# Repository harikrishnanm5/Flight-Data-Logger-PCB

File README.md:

# Crash-Safe UAV Flight Data Logger PCB

-0277BD?style=flat-square)

A compact **50.0 × 50.0 mm, 4-layer** crash-safe UAV flight data logger ("black box") hardware design built on the standard **30.5 × 30.5 mm M3 flight-controller stack** footprint.

Designed around an **STM32F446RET6** Cortex-M4F MCU, **ESP32-WROOM-32E** Wi-Fi/BLE telemetry module, **6-axis IMU + barometer**, dual **SPI FRAM + MicroSD** storage, an **ideal-diode PowerPath + 1.0 F supercapacitor** backup stage, hardware **3.00 V power-fail detection**, and a high-intensity optical recovery beacon.

---

## Key Features

- **Crash-Safe Power Holdup & Brownout Trigger**:
  - 3.7 V Li-ion input (`J1`) protected by a reverse-polarity P-MOSFET (`Q1`, `AO3401A`).
  - Dual `LTC4412ES6` ideal-diode PowerPath controllers (`U7`/`Q2` and `U8`/`Q3`) seamlessly OR-ing the main battery (`V_BAT_PROT`) and a **5.5 V / 1.0 F backup supercapacitor** (`C_SC1`) onto `V_SYS`.
  - Slew-limited supercapacitor charger (`U11`, `AP22814AW5`) with current-limiting resistor (`R24`, 15 Ω) and Schottky blocking diode (`D4`, `B5819W`).
  - High-efficiency 3.3 V / 2 A synchronous buck regulator (`U6`, `TPS62822DLC`) with shielded `1.0 µH` inductor (`L1`) and filtered `+3.3VA` analog rail (`FB1`).
  - Precision **3.00 V Power-Fail Detect (PFD)** comparator (`U9`, `TLV7031DBV`) referenced against a 2.500 V shunt reference (`U10`, `LM4040DBZ-2.5`) asserting `PFD_INT` on MCU `EXTI1` to flush telemetry before holdup collapse.
  - 0.1%-tolerance battery voltage sensing divider (`R1`/`R2` -> `V_BAT_ADC`).
- **Dual-Tier Flight Recording**:
  - **2 Mbit SPI FRAM** (`U5`, `CY15B102QN-50SXIT`) for deterministic, zero-wear, instant-write black-box buffering during power loss.
  - **Push-Pull MicroSD Socket** (`J3`, Hirose `DM3D-SF`) on `SPI1` with card-detect (`SD_CD`) and pull-ups.
- **Flight Sensors**:
  - **6-Axis IMU** (`U3`, `MPU-6050`, I2C `0x68`) with dedicated `MPU_INT` line.
  - **Barometric Pressure Sensor** (`U4`, `BMP280`, I2C `0x76`).
- **Telemetry & Recovery Beacon**:
  - **ESP32-WROOM-32E-N4** (`U2`) wired to `USART1` (`R16`/`R17` series resistors) with dedicated PCB top-edge antenna keepout zone (`y < 6.25 mm`).
  - **High-intensity red optical beacon LED** (`D1`, `SM2835-RED-HI`) switched via N-MOSFET (`Q4`, `2N7002`).

---

## System Architecture

```mermaid
flowchart LR
    BATT["3.7V Li-ion Input (J1)"] --> RVP["Reverse-Polarity PFET (Q1)"]
    RVP --> CHG["Supercap Charger (U11 + R24 + D4)"]
    CHG --> SCAP["1.0F 5.5V Supercap (C_SC1)"]

    RVP --> OR1["Ideal Diode Ctrl (U7 + Q2)"]
    SCAP --> OR2["Ideal Diode Ctrl (U8 + Q3)"]
    OR1 --> VSYS["V_SYS"]
    OR2 --> VSYS

    VSYS --> BUCK["3.3V 2A Buck (U6 TPS62822 + L1)"]
    BUCK --> V33["+3V3 Plane (In2.Cu)"]
    V33 --> FB["Ferrite Bead (FB1)"] --> V33A["+3.3VA Analog"]

    RVP --> PFD["3.00V PFD (U9 TLV7031 + U10 LM4040)"]
    RVP --> ADC["0.1% Divider (R1/R2)"]
    PFD -->|PFD_INT| MCU["STM32F446RET6 (U1)"]
    ADC -->|V_BAT_ADC| MCU

    MCU <-->|I2C1| IMU["MPU-6050 (U3)"]
    MCU <-->|I2C1| BARO["BMP280 (U4)"]
    MCU <-->|SPI1| FRAM["2Mbit FRAM (U5)"]
    MCU <-->|SPI1| SD["MicroSD (J3)"]
    MCU <-->|USART1| ESP["ESP32-WROOM-32E (U2)"]
    MCU -->|BEACON_CTRL| BEACON["Q4 + D1 Beacon LED"]
```

---

## PCB & Stackup Specifications

| Parameter | Specification |
| :--- | :--- |
| **Board Outline** | 50.0 × 50.0 mm, 2.5 mm corner radius |
| **Thickness** | 1.6 mm |
| **Mounting Pattern** | 30.5 × 30.5 mm M3 (`H1`–`H4`, 3.2 mm drill, 6.4 mm grounded pad) |
| **Copper Layers** | **4 Layers** (`F.Cu`, `In1.Cu`, `In2.Cu`, `B.Cu`) |
| **Layer 1 (`F.Cu`)** | Top components (42 footprints), signals, `GND` copper pour |
| **Layer 2 (`In1.Cu`)** | Solid `GND` reference plane |
| **Layer 3 (`In2.Cu`)** | `+3V3` power plane |
| **Layer 4 (`B.Cu`)** | Bottom components (59 footprints), signals, `GND` copper pour |
| **PCB Geometry Counts** | 101 footprints, 848 track segments, 272 vias, 4 copper zones, 57 nets |
| **Min Clearance / Edge** | 0.20 mm clearance / 0.30 mm copper-to-edge clearance |
| **Min Track / Via** | 0.15 mm track / 0.45 mm via dia (0.20 mm drill, 0.125 mm annular ring) |
| **Hole-to-Hole Clearance** | 0.50 mm minimum |

---

## Key Components

> Full 51-line / 101-footprint bill of materials is available in [`BOM.csv`](BOM.csv) (97 electrical components + 4 grounded M3 mounting holes).

| Ref | Part / Value | MPN | Side | Function |
| :--- | :--- | :--- | :--- | :--- |
| `U1` | `STM32F446RET6` | `STM32F446RET6` | Top | ARM Cortex-M4F MCU (180 MHz, 512 KB Flash, LQFP-64) |
| `U2` | `ESP32-WROOM-32` | `ESP32-WROOM-32E-N4` | Top | Wi-Fi / BLE Telemetry Module |
| `U3` | `MPU-6050` | `MPU-6050` | Top | 6-Axis IMU (`I2C1` `0x68`) |
| `U4` | `BMP280` | `BMP280` | Top | Barometric Pressure Sensor (`I2C1` `0x76`) |
| `U5` | `CY15B102QN-50SXIT` | `CY15B102QN-50SXIT` | Bottom | 2 Mbit SPI FRAM Non-Volatile Buffer |
| `U6` | `TPS62822DLC` | `TPS62822DLCR` | Bottom | 3.3 V 2 A Synchronous Buck Regulator |
| `U7`, `U8` | `LTC4412ES6` | `LTC4412ES6#TRPBF` | Bottom | Battery & Supercap Ideal Diode OR-ing Controllers |
| `U9` | `TLV7031DBV` | `TLV7031DBVR` | Bottom | Power-Fail Detect Comparator (3.00 V Trip) |
| `U10` | `LM4040DBZ-2.5` | `LM4040AIM3-2.5` | Bottom | 2.500 V Precision Shunt Reference |
| `U11` | `AP22814AW5` | `AP22814AW5-7` | Bottom | Slew-Limited Supercapacitor Charge Switch |
| `C_SC1` | `1.0F 5.5V` | `DX-5R5V105U` | Top (THT) | 5.5 V 1.0 F Backup Supercapacitor |
| `J3` | `MicroSD_SPI` | `DM3D-SF` | Top | Push-Pull MicroSD Card Socket (`SPI1`) |
| `J1` | `JST_PH_BATT` | `B2B-PH-K-S` | Top (THT) | 3.7 V Li-ion Input Header |
| `J2` | `SWD_5P` | `HDR-1x5-2.54` | Top (THT) | SWD Debug Header (`3V3`, `SWCLK`, `GND`, `SWDIO`, `NRST`) |
| `J4` | `ESP_UART_6P` | `HDR-1x6-1.27` | Top (THT) | ESP32 UART/Flash Header |
| `D1` | `BEACON_LED_HI` | `SM2835-RED-HI` | Top | High-Intensity Optical Emergency Beacon LED |

---

## Repository Structure

```text
.
├── FlightDataLogger.kicad_pro          # KiCad project & DRC/netclass settings
├── FlightDataLogger.kicad_sch          # KiCad schematic (A2 sheet)
├── FlightDataLogger.kicad_pcb          # KiCad 4-layer PCB layout
├── BOM.csv                             # Complete BOM generated from design_spec.py
├── layers/                             # Exported copper & outline plots (PDF / SVG)
│   ├── FlightDataLogger-F_Cu.pdf
│   ├── FlightDataLogger-F_Cu.svg
│   ├── FlightDataLogger-In1_Cu.pdf
│   ├── FlightDataLogger-In2_Cu.pdf
│   ├── FlightDataLogger-B_Cu.pdf
│   ├── FlightDataLogger-Edge_Cuts.pdf
│   └── FlightDataLogger-Edge_Cuts.svg
└── scripts/                            # Programmatic KiCad generation & verification
    ├── design_spec.py                  # Single source of truth (board, components, nets)
    ├── generate_project_and_schematic.py
    ├── generate_pcb.py                 # KiCad pcbnew API generator + Pathfinder A* router
    └── verify_placement.py             # Footprint, bounds, keepout & courtyard checker
```

---

## Layer Plots

Exported fabrication layer plots are available in [`layers/`](layers/):

- Top Copper (`F.Cu`): [`FlightDataLogger-F_Cu.pdf`](layers/FlightDataLogger-F_Cu.pdf) | [`FlightDataLogger-F_Cu.svg`](layers/FlightDataLogger-F_Cu.svg)
- Inner 1 (`In1.Cu` — Solid GND): [`FlightDataLogger-In1_Cu.pdf`](layers/FlightDataLogger-In1_Cu.pdf)
- Inner 2 (`In2.Cu` — +3V3 Plane): [`FlightDataLogger-In2_Cu.pdf`](layers/FlightDataLogger-In2_Cu.pdf)
- Bottom Copper (`B.Cu`): [`FlightDataLogger-B_Cu.pdf`](layers/FlightDataLogger-B_Cu.pdf)
- Board Outline (`Edge.Cuts`): [`FlightDataLogger-Edge_Cuts.pdf`](layers/FlightDataLogger-Edge_Cuts.pdf) | [`FlightDataLogger-Edge_Cuts.svg`](layers/FlightDataLogger-Edge_Cuts.svg)

---

## Programmatic Generation & Verification

The hardware files can also be inspected or regenerated programmatically from [`scripts/design_spec.py`](scripts/design_spec.py):

```bash
# 1. Verify footprint loading, bounds, antenna keepout, and courtyard collisions
python scripts/verify_placement.py

# 2. Generate .kicad_pro and .kicad_sch
python scripts/generate_project_and_schematic.py

# 3. Generate .kicad_pcb (run using KiCad's Python environment with pcbnew)
python scripts/generate_pcb.py
```

> **Note:** The generator and verification scripts currently reference local KiCad library directories (`SYM_DIR` / `FP_ROOT` / `FP_DIR` set to `D:\FOSSEE\KiCad\share\kicad\...`) and write KiCad 6.0 `pcbnew` output (while [`FlightDataLogger.kicad_pcb`](FlightDataLogger.kicad_pcb) in this repo has subsequently been updated and saved in KiCad 10.0). Adjust those library paths to match your KiCad installation before re-running the scripts.

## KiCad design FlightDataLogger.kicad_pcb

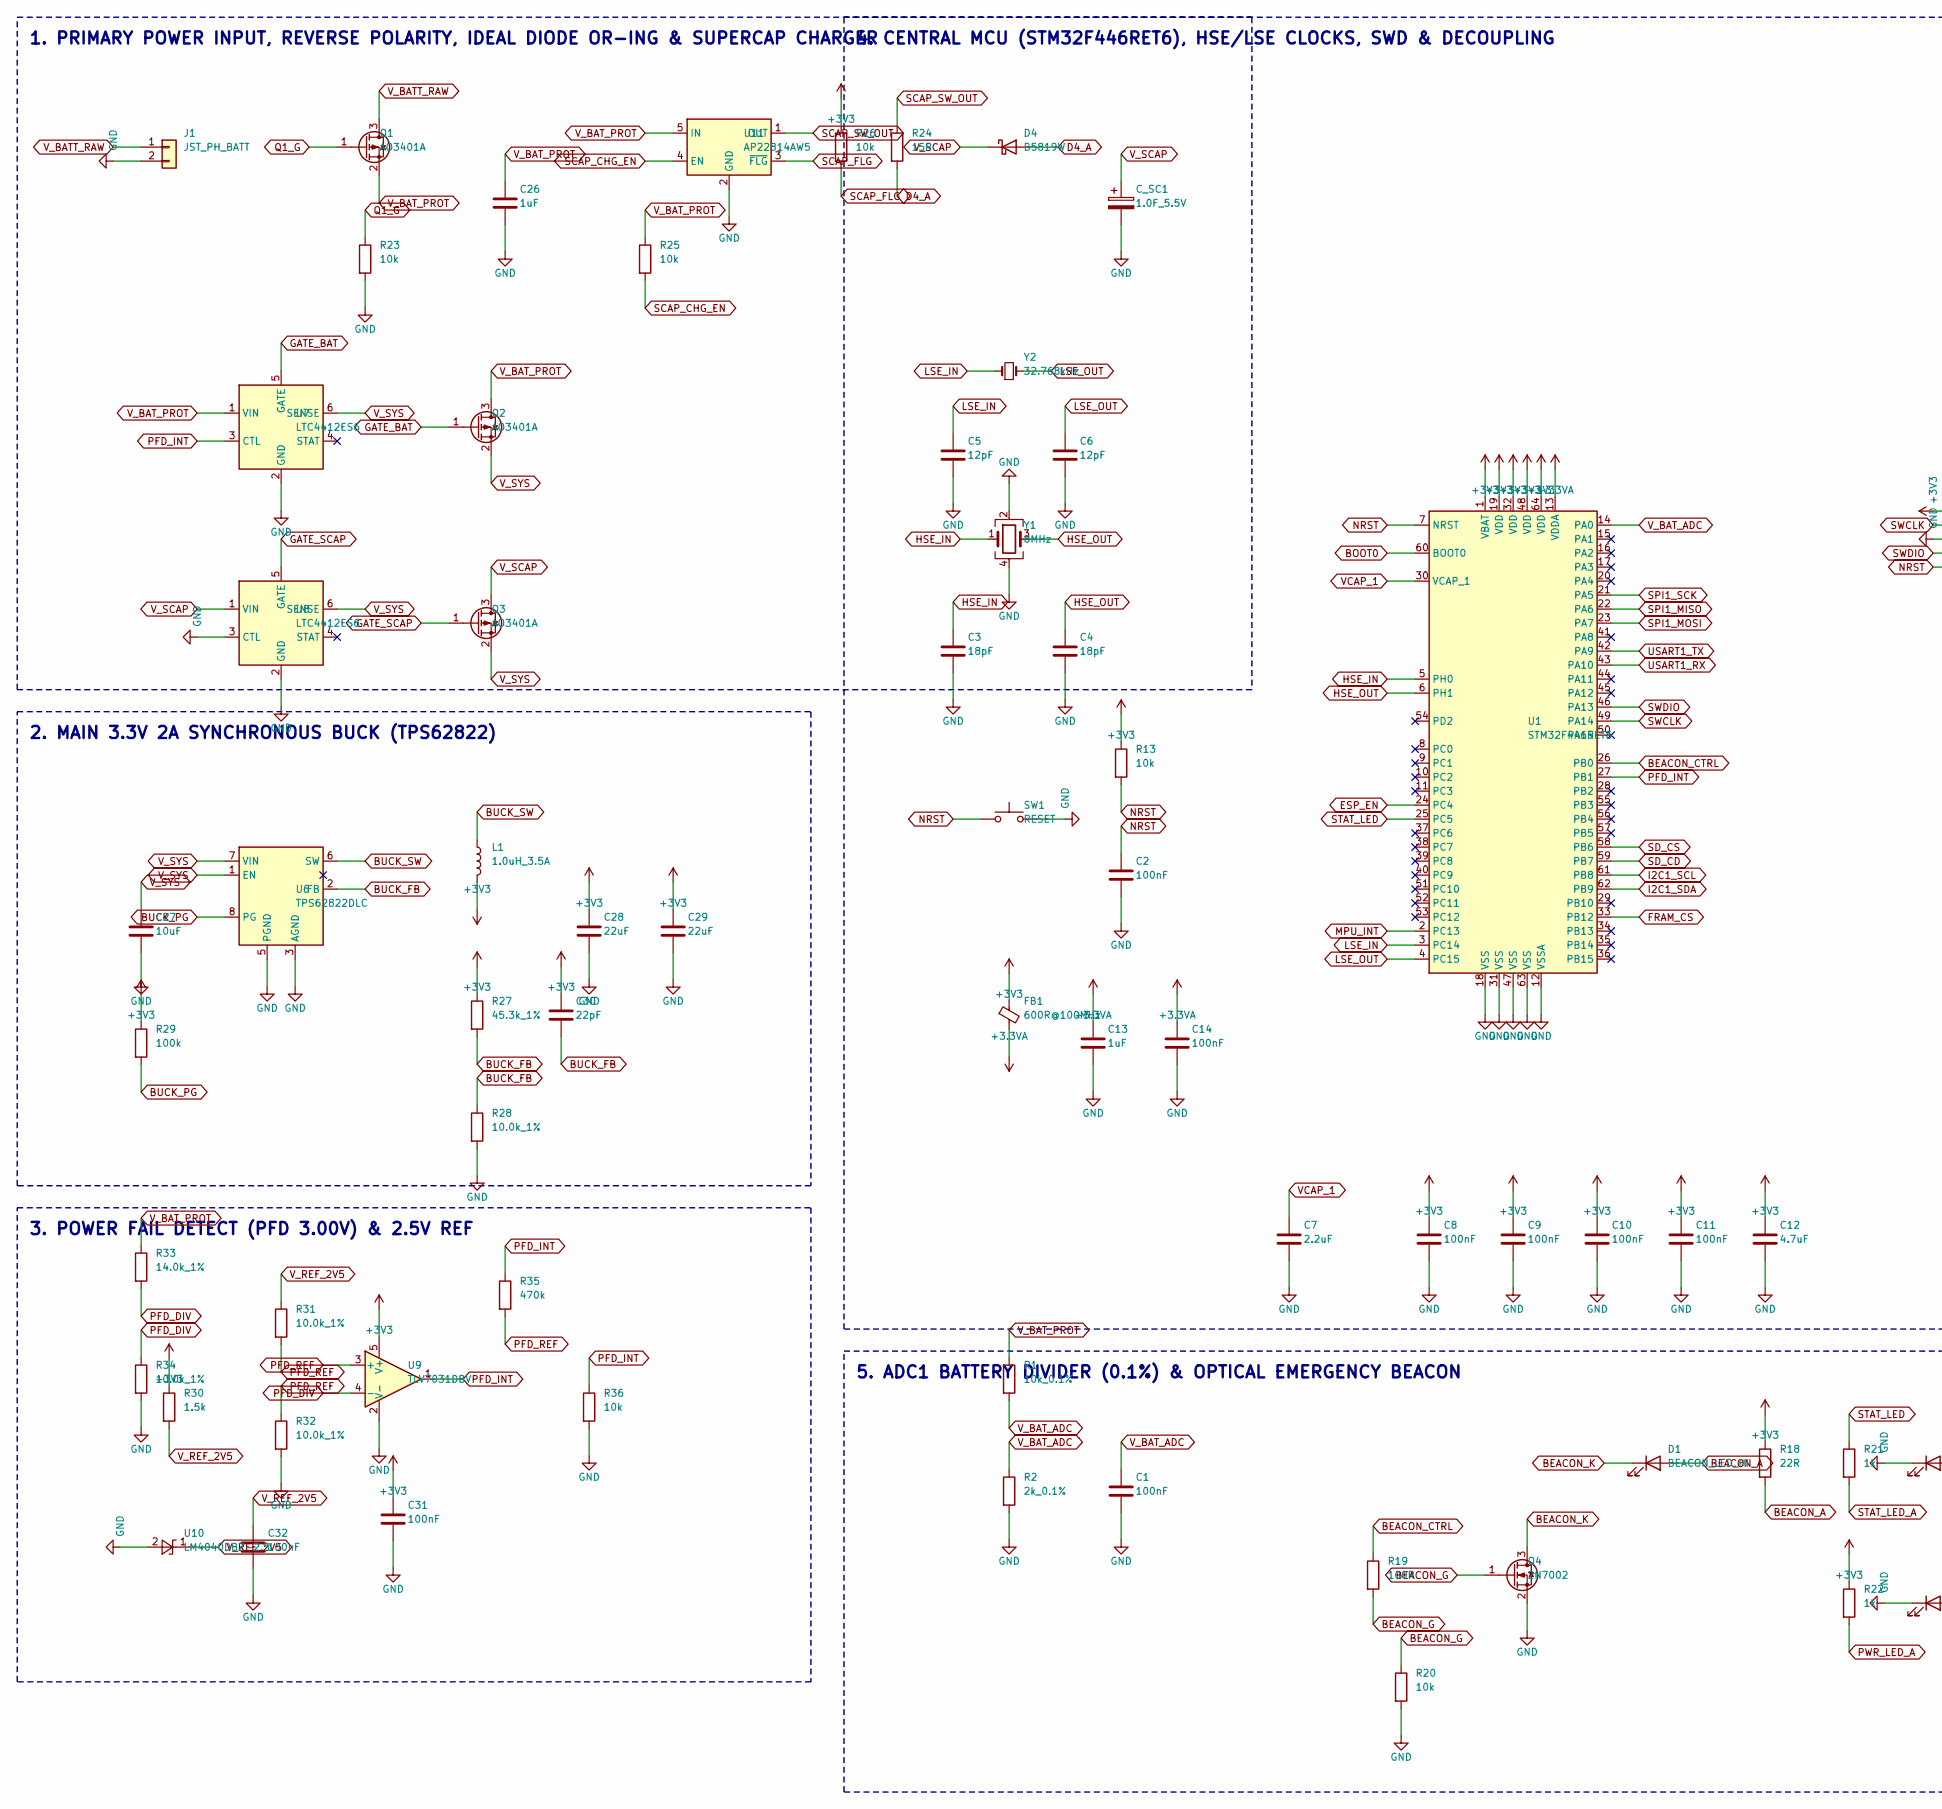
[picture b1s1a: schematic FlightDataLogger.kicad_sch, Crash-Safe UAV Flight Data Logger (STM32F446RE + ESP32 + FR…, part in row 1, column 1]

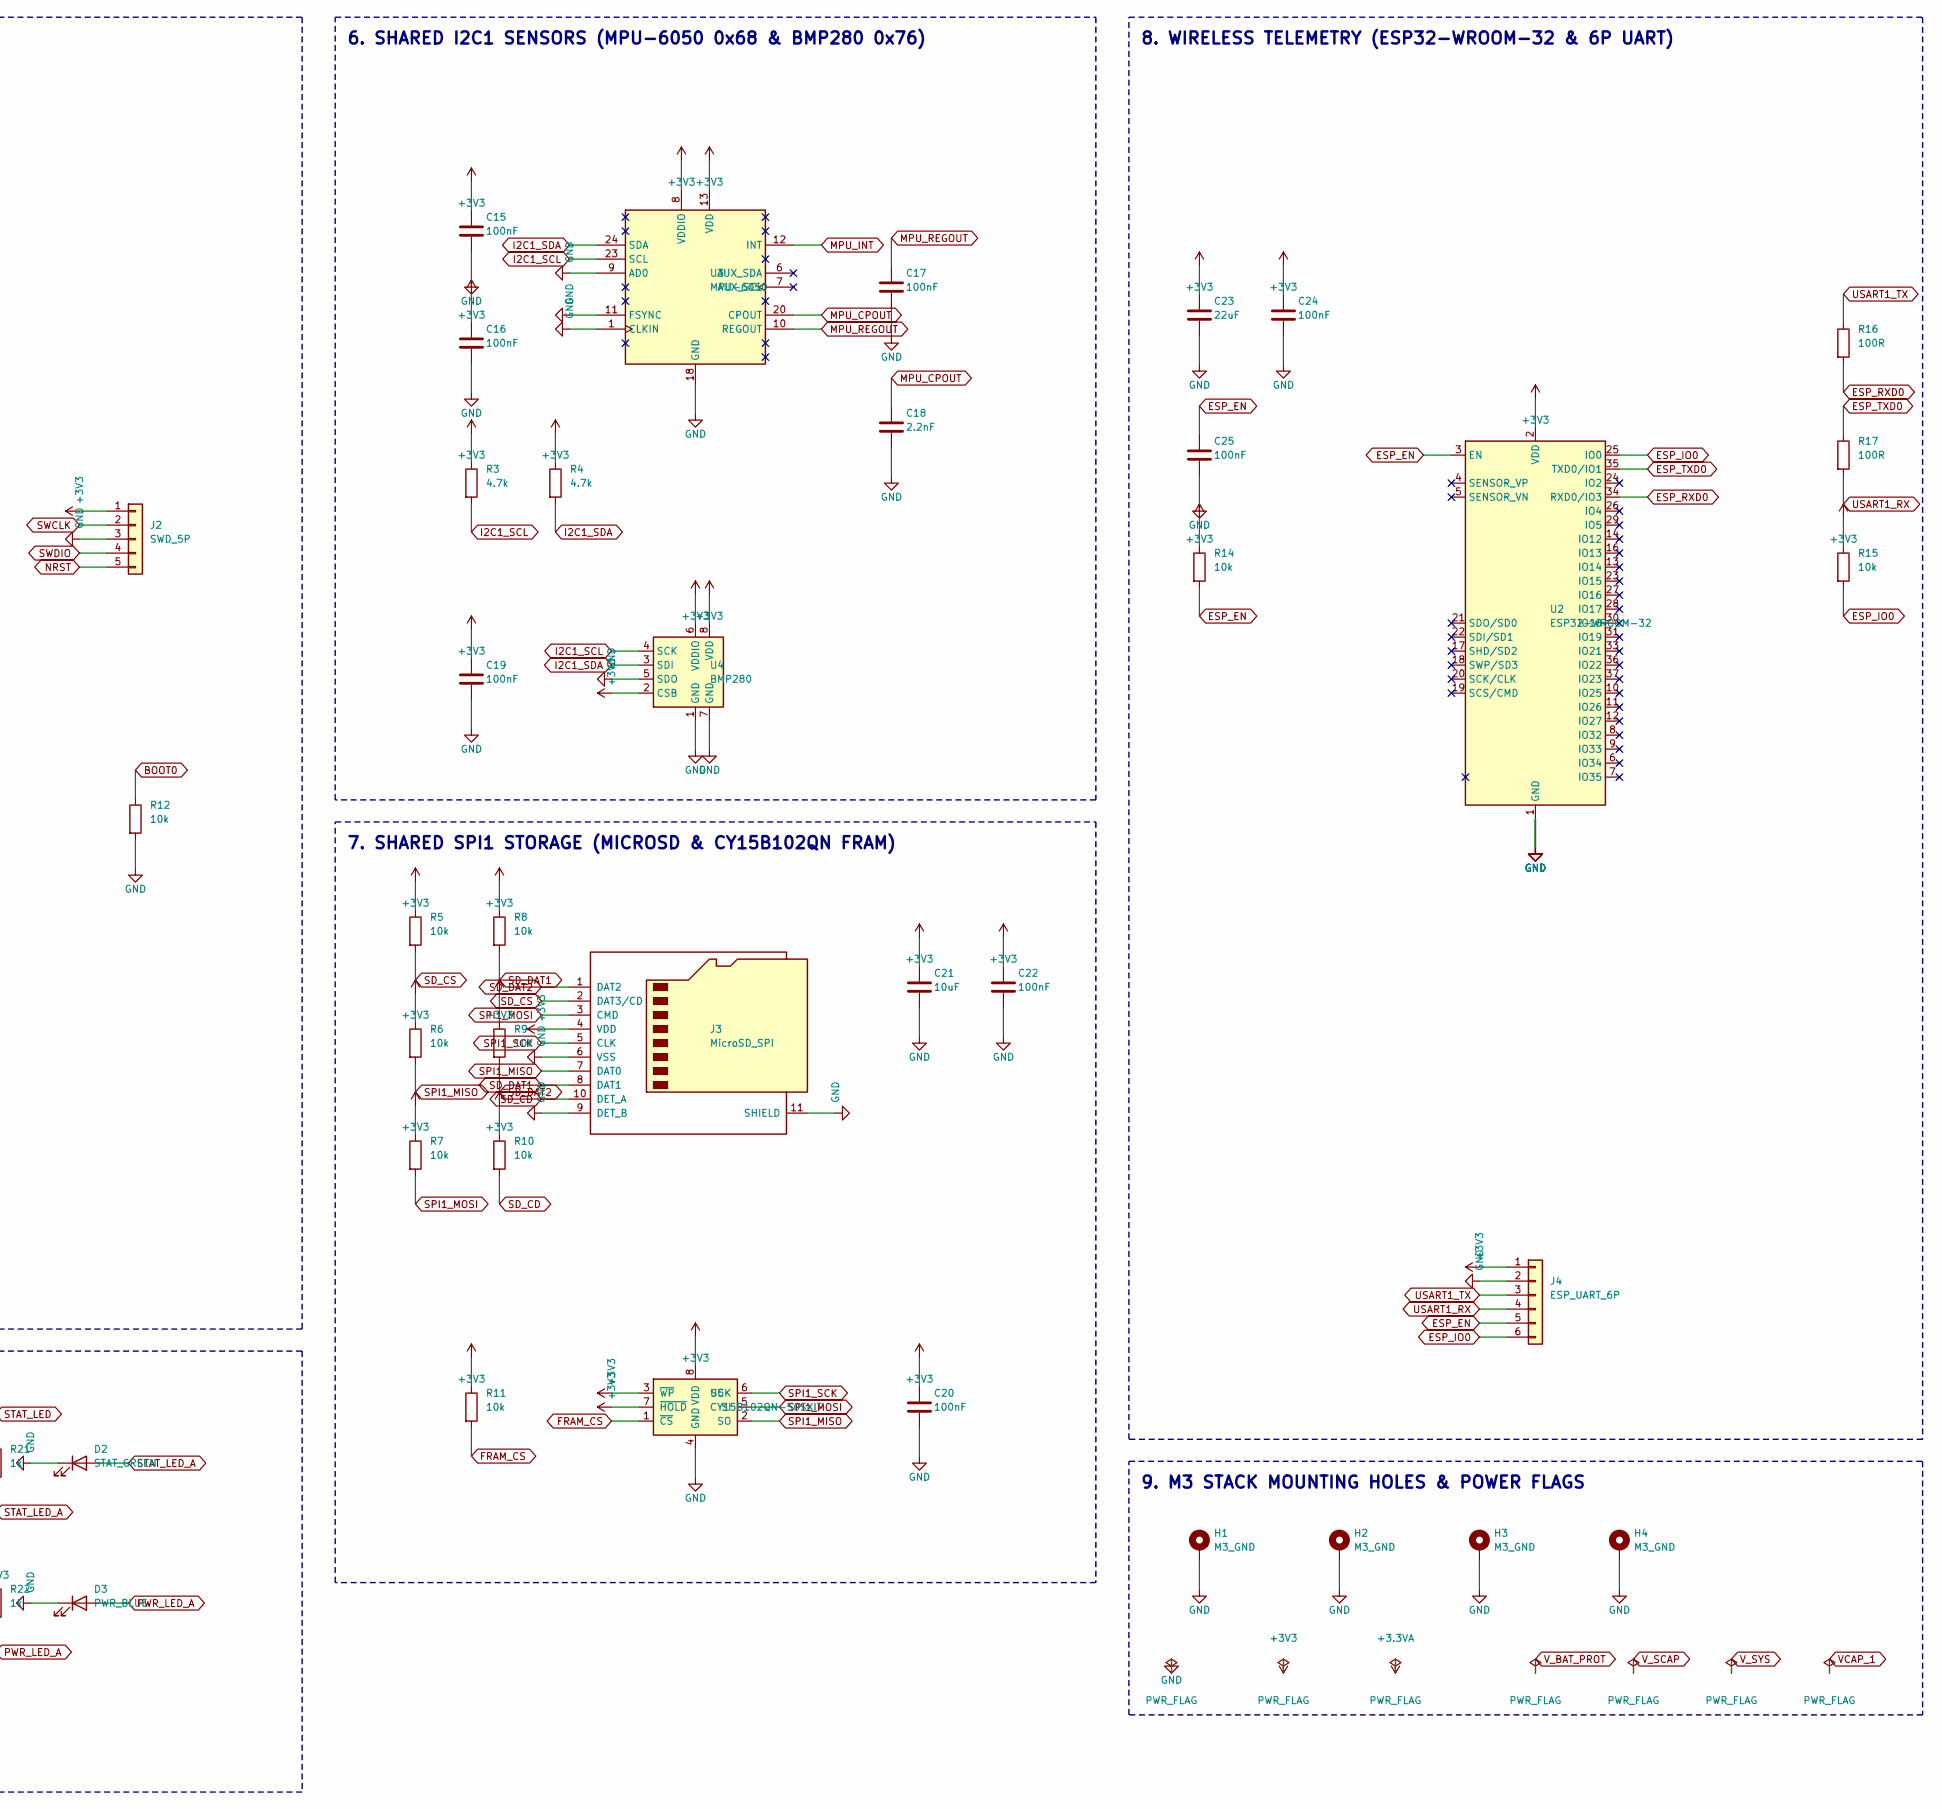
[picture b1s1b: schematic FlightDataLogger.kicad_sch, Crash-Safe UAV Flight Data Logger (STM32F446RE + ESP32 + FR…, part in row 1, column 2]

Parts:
C1, C2, C8, C9, C10, C11, C14, C15, C16, C17, C19, C20, C22, C24, C25, C31, C32: 100nF; C_0603_1608Metric; MPN CC0603KRX7R7BB104
C3, C4: 18pF; C_0603_1608Metric; MPN CC0603JRNPO9BN180
C5, C6: 12pF; C_0603_1608Metric; MPN CC0603JRNPO9BN120
C7: 2.2uF; C_0603_1608Metric; MPN CL10A225KQ8NNNC
C12: 4.7uF; C_0603_1608Metric; MPN CL10A475KQ8NNNC
C13, C26: 1uF; C_0603_1608Metric; MPN CL10A105KB8NNNC
C18: 2.2nF; C_0603_1608Metric; MPN CC0603KRX7R9BB222
C21, C27: 10uF; C_0805_2012Metric; MPN CL21A106KAYNNNE
C23, C28, C29: 22uF; C_0805_2012Metric; MPN CL21A226MAYNNNE
C30: 22pF; C_0603_1608Metric; MPN CC0603JRNPO9BN220
C_SC1: 1.0F_5.5V; DX_5R5VxxxxU_D11.5mm_P5.00mm; MPN DX-5R5V105U
D1: BEACON_LED_HI; LED_PLCC_2835; MPN SM2835-RED-HI
D2: STAT_GREEN; LED_0603_1608Metric; MPN LTST-C190KGKT
D3: PWR_BLUE; LED_0603_1608Metric; MPN LTST-C190TBKT
D4: B5819W; D_SOD-123; MPN B5819W-7-F
FB1: 600R@100MHz; L_0603_1608Metric; MPN BLM18AG601SN1D
H1, H2, H3, H4: M3_GND; MountingHole_3.2mm_M3_Pad_TopBottom; MPN M3_HOLE
J1: JST_PH_BATT; JST_PH_B2B-PH-K_1x02_P2.00mm_Vertical; MPN B2B-PH-K-S
J2: SWD_5P; PinHeader_1x05_P2.54mm_Vertical; MPN HDR-1x5-2.54
J3: MicroSD_SPI; microSD_HC_Hirose_DM3D-SF; MPN DM3D-SF
J4: ESP_UART_6P; PinHeader_1x06_P1.27mm_Vertical; MPN HDR-1x6-1.27
L1: 1.0uH_3.5A; L_Wuerth_MAPI-3015; MPN 74438334010
Q1, Q2, Q3: AO3401A; SOT-23; MPN AO3401A
Q4: 2N7002; SOT-23; MPN 2N7002LT1G
R1: 10k_0.1%; R_0603_1608Metric; MPN ERA-3AEB103V
R2: 2k_0.1%; R_0603_1608Metric; MPN ERA-3AEB202V
R3, R4: 4.7k; R_0603_1608Metric; MPN RC0603FR-074K7L
R5, R6, R7, R8, R9, R10, R11, R12, R13, R14, R15, R20, R23, R25, R26, R36: 10k; R_0603_1608Metric; MPN RC0603FR-0710KL
R16, R17, R19: 100R; R_0603_1608Metric; MPN RC0603FR-07100RL
R18: 22R; R_0805_2012Metric; MPN ERJ-6GEYJ220V
R21, R22: 1k; R_0603_1608Metric; MPN RC0603FR-071KL
R24: 15R; R_0805_2012Metric; MPN ERJ-6GEYJ150V
R27: 45.3k_1%; R_0603_1608Metric; MPN RC0603FR-0745K3L
R28, R31, R32, R34: 10.0k_1%; R_0603_1608Metric; MPN RC0603FR-0710KL
R29: 100k; R_0603_1608Metric; MPN RC0603FR-07100KL
R30: 1.5k; R_0603_1608Metric; MPN RC0603FR-071K5L
R33: 14.0k_1%; R_0603_1608Metric; MPN RC0603FR-0714KL
R35: 470k; R_0603_1608Metric; MPN RC0603FR-07470KL
SW1: RESET; SW_SPST_CK_KXT3; MPN KXT311LHS
U1: STM32F446RET6; LQFP-64_10x10mm_P0.5mm; MPN STM32F446RET6
U2: ESP32-WROOM-32; MPN ESP32-WROOM-32E-N4
U3: MPU-6050; InvenSense_QFN-24_4x4mm_P0.5mm; MPN MPU-6050
U4: BMP280; Bosch_LGA-8_2x2.5mm_P0.65mm_ClockwisePinNumbering; MPN BMP280
U5: CY15B102QN-50SXIT; SOIC-8_3.9x4.9mm_P1.27mm; MPN CY15B102QN-50SXIT
U6: TPS62822DLC; Texas_VSON-HR-8_1.5x2mm_P0.5mm; MPN TPS62822DLCR
U7, U8: LTC4412ES6; TSOT-23-6; MPN LTC4412ES6#TRPBF
U9: TLV7031DBV; SOT-23-5; MPN TLV7031DBVR
U10: LM4040DBZ-2.5; SOT-23; MPN LM4040AIM3-2.5
U11: AP22814AW5; SOT-23-5; MPN AP22814AW5-7
Y1: 8MHz; Crystal_SMD_3225-4Pin_3.2x2.5mm; MPN ABM8-8.000MHZ-B2-T
Y2: 32.768kHz; Crystal_SMD_3215-2Pin_3.2x1.5mm; MPN ABS07-32.768KHZ-T

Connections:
+3.3VA: C13.1, C14.1, FB1.2, U1.13 (VDDA)
+3V3: C8.1, C9.1, C10.1, C11.1, C12.1, C15.1, C16.1, C19.1, C20.1, C21.1, C22.1, C23.1, C24.1, C28.1, C29.1, C30.1, C31.1, FB1.1, J2.1, J3.4 (VDD), J4.1, L1.2, R3.1, R4.1, R5.1, R6.1, R7.1, R8.1, R9.1, R10.1, R11.1, R13.1, R14.1, R15.1, R18.1, R22.1, R26.1, R27.1, R29.1, R30.1, U1.1 (VBAT), U1.19 (VDD), U1.32 (VDD), U1.48 (VDD), U1.64 (VDD), U2.2 (VDD), U3.8 (VDDIO), U3.13 (VDD), U4.2 (CSB), U4.6 (VDDIO), U4.8 (VDD), U5.3 (~WP), U5.7 (~HOLD), U5.8 (VDD), U9.5 (V+)
BEACON_A: D1.2 (A), R18.2
BEACON_CTRL: R19.1, U1.26 (PB0)
BEACON_G: Q4.1 (G), R19.2, R20.1
BEACON_K: D1.1 (K), Q4.3 (D)
BOOT0: R12.1, U1.60 (BOOT0)
BUCK_FB: C30.2, R27.2, R28.1, U6.2 (FB)
BUCK_PG: R29.2, U6.8 (PG)
BUCK_SW: L1.1, U6.6 (SW)
D4_A: D4.2 (A), R24.2
ESP_EN: C25.1, J4.5, R14.2, U1.24 (PC4), U2.3 (EN)
ESP_IO0: J4.6, R15.2, U2.25 (IO0)
ESP_RXD0: R16.2, U2.34 (RXD0/IO3)
ESP_TXD0: R17.1, U2.35 (TXD0/IO1)
FRAM_CS: R11.2, U1.33 (PB12), U5.1 (~CS)
GATE_BAT: Q2.1 (G), U7.5 (GATE)
GATE_SCAP: Q3.1 (G), U8.5 (GATE)
GND: C1.2, C2.2, C3.2, C4.2, C5.2, C6.2, C7.2, C8.2, C9.2, C10.2, C11.2, C12.2, C13.2, C14.2, C15.2, C16.2, C17.2, C18.2, C19.2, C20.2, C21.2, C22.2, C23.2, C24.2, C25.2, C26.2, C27.2, C28.2, C29.2, C31.2, C32.2, C_SC1.2, D2.1 (K), D3.1 (K), H1.1, H2.1, H3.1, H4.1, J1.2, J2.3, J3.6 (VSS), J3.9 (DET_B), J3.11 (SHIELD), J4.2, Q4.2 (S), R2.2, R12.2, R20.2, R23.2, R28.2, R32.2, R34.2, R36.2, SW1.2, U1.12 (VSSA), U1.18 (VSS), U1.31 (VSS), U1.47 (VSS), U1.63 (VSS), U2.1 (GND), U2.15 (GND), U2.38 (GND), U2.39 (GND), U3.1 (CLKIN), U3.9 (AD0), U3.11 (FSYNC), U3.18 (GND), U4.1 (GND), U4.5 (SDO), U4.7 (GND), U5.4 (GND), U6.3 (AGND), U6.5 (PGND), U7.2 (GND), U8.2 (GND), U8.3 (CTL), U9.2 (V-), U10.2 (A), U11.2 (GND), Y1.2, Y1.4
HSE_IN: C3.1, U1.5 (PH0), Y1.1
HSE_OUT: C4.1, U1.6 (PH1), Y1.3
I2C1_SCL: R3.2, U1.61 (PB8), U3.23 (SCL), U4.4 (SCK)
I2C1_SDA: R4.2, U1.62 (PB9), U3.24 (SDA), U4.3 (SDI)
LSE_IN: C5.1, U1.3 (PC14), Y2.1
LSE_OUT: C6.1, U1.4 (PC15), Y2.2
MPU_CPOUT: C18.1, U3.20 (CPOUT)
MPU_INT: U1.2 (PC13), U3.12 (INT)
MPU_REGOUT: C17.1, U3.10 (REGOUT)
NRST: C2.1, J2.5, R13.2, SW1.1, U1.7 (NRST)
PFD_DIV: R33.2, R34.1, U9.4 (-)
PFD_INT: R35.1, R36.1, U1.27 (PB1), U7.3 (CTL), U9.1
PFD_REF: R31.2, R32.1, R35.2, U9.3 (+)
PWR_LED_A: D3.2 (A), R22.2
Q1_G: Q1.1 (G), R23.1
SCAP_CHG_EN: R25.2, U11.4 (EN)
SCAP_FLG: R26.2, U11.3 (~FLG)
SCAP_SW_OUT: R24.1, U11.1 (OUT)
SD_CD: J3.10 (DET_A), R10.2, U1.59 (PB7)
SD_CS: J3.2 (DAT3/CD), R5.2, U1.58 (PB6)
SD_DAT1: J3.8 (DAT1), R8.2
SD_DAT2: J3.1 (DAT2), R9.2
SPI1_MISO: J3.7 (DAT0), R6.2, U1.22 (PA6), U5.2 (SO)
SPI1_MOSI: J3.3 (CMD), R7.2, U1.23 (PA7), U5.5 (SI)
SPI1_SCK: J3.5 (CLK), U1.21 (PA5), U5.6 (SCK)
STAT_LED: R21.1, U1.25 (PC5)
STAT_LED_A: D2.2 (A), R21.2
SWCLK: J2.2, U1.49 (PA14)
SWDIO: J2.4, U1.46 (PA13)
USART1_RX: J4.4, R17.2, U1.43 (PA10)
USART1_TX: J4.3, R16.1, U1.42 (PA9)
VCAP_1: C7.1, U1.30 (VCAP_1)
V_BATT_RAW: J1.1, Q1.3 (D)
V_BAT_ADC: C1.1, R1.2, R2.1, U1.14 (PA0)
V_BAT_PROT: C26.1, Q1.2 (S), Q2.3 (D), R1.1, R25.1, R33.1, U7.1 (VIN), U11.5 (IN)
V_REF_2V5: C32.1, R30.2, R31.1, U10.1 (K)
V_SCAP: C_SC1.1, D4.1 (K), Q3.3 (D), U8.1 (VIN)
V_SYS: C27.1, Q2.2 (S), Q3.2 (S), U6.1 (EN), U6.7 (VIN), U7.6 (SENSE), U8.6 (SENSE)

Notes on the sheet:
1. PRIMARY POWER INPUT, REVERSE POLARITY, IDEAL DIODE OR-ING & SUPERCAP CHARGER
2. MAIN 3.3V 2A SYNCHRONOUS BUCK (TPS62822)
3. POWER FAIL DETECT (PFD 3.00V) & 2.5V REF
4. CENTRAL MCU (STM32F446RET6), HSE/LSE CLOCKS, SWD & DECOUPLING
5. ADC1 BATTERY DIVIDER (0.1%) & OPTICAL EMERGENCY BEACON
6. SHARED I2C1 SENSORS (MPU-6050 0x68 & BMP280 0x76)
7. SHARED SPI1 STORAGE (MICROSD & CY15B102QN FRAM)
8. WIRELESS TELEMETRY (ESP32-WROOM-32 & 6P UART)
9. M3 STACK MOUNTING HOLES & POWER FLAGS

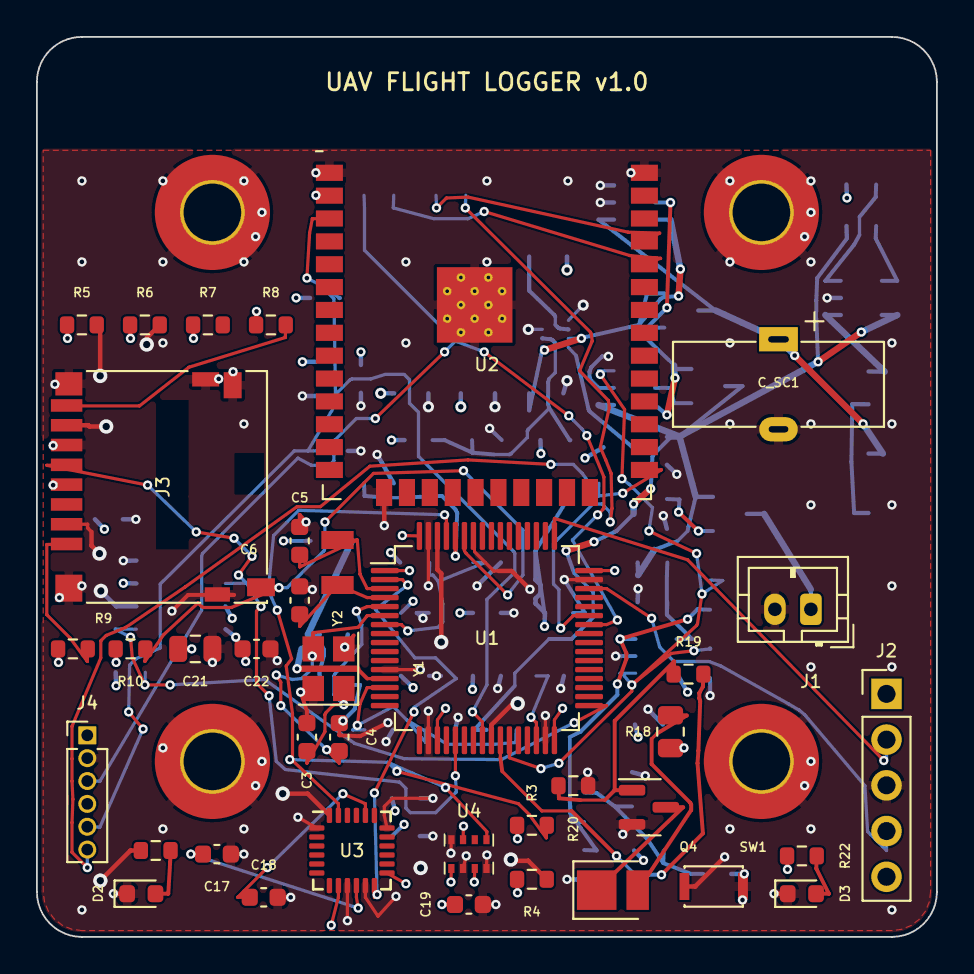
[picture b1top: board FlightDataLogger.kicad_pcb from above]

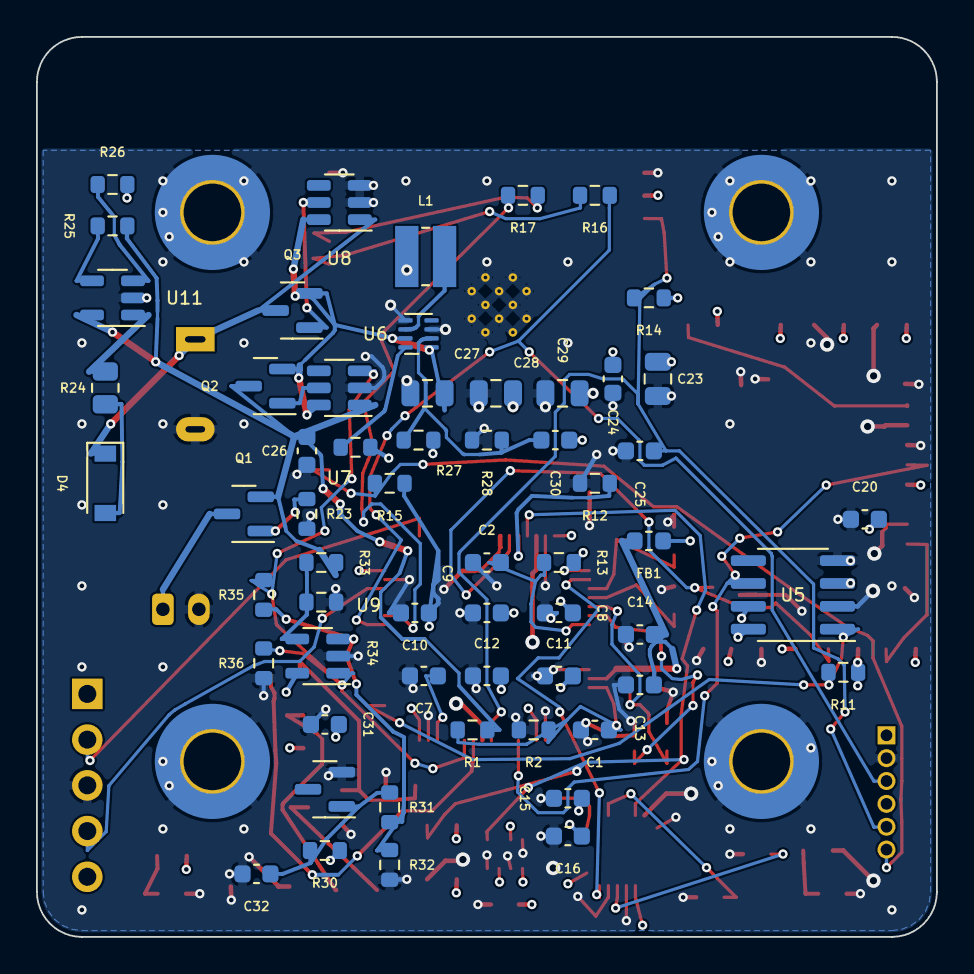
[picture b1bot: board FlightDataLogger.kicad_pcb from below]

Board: 4 copper layers, 50.0 x 50.0 mm, 101 parts (59 on the bottom side), 57 nets.

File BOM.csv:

Designators,Qty,Value,Footprint,MPN,Placement_Side,Description
"H1, H2, H3, H4",4,M3_GND,MountingHole_3.2mm_M3_Pad_TopBottom,M3_HOLE,F,M3 Drone Stack Hole NW; M3 Drone Stack Hole NE; M3 Drone Stack Hole SW ...
U2,1,ESP32-WROOM-32,ESP32-WROOM-32,ESP32-WROOM-32E-N4,F,Wi-Fi/BLE Telemetry Module
U1,1,STM32F446RET6,LQFP-64_10x10mm_P0.5mm,STM32F446RET6,F,ARM Cortex-M4F MCU 180MHz 512KB
U3,1,MPU-6050,InvenSense_QFN-24_4x4mm_P0.5mm,MPU-6050,F,"6-Axis IMU (I2C 0x68, AD0=GND)"
U4,1,BMP280,Bosch_LGA-8_2x2.5mm_P0.65mm_ClockwisePinNumbering,BMP280,F,Barometric Pressure Sensor (I2C 0x76)
J3,1,MicroSD_SPI,microSD_HC_Hirose_DM3D-SF,DM3D-SF,F,MicroSD Card Push-Pull Socket (SPI)
C_SC1,1,1.0F_5.5V,DX_5R5VxxxxU_D11.5mm_P5.00mm,DX-5R5V105U,F,5.5V 1.0F Backup Supercapacitor
J1,1,JST_PH_BATT,JST_PH_B2B-PH-K_1x02_P2.00mm_Vertical,B2B-PH-K-S,F,3.7V Li-ion Input JST-PH 2-Pin
J2,1,SWD_5P,PinHeader_1x05_P2.54mm_Vertical,HDR-1x5-2.54,F,"SWD Debug (3V3, SWCLK, GND, SWDIO, NRST)"
J4,1,ESP_UART_6P,PinHeader_1x06_P1.27mm_Vertical,HDR-1x6-1.27,F,ESP32 UART/Flash 6-Pin Header
SW1,1,RESET,SW_SPST_CK_KXT3,KXT311LHS,F,MCU Reset Tactile Switch
D1,1,BEACON_LED_HI,LED_PLCC_2835,SM2835-RED-HI,F,High-Intensity Optical Emergency Beacon LED
D2,1,STAT_GREEN,LED_0603_1608Metric,LTST-C190KGKT,F,Status / Logger Activity LED (PC5)
D3,1,PWR_BLUE,LED_0603_1608Metric,LTST-C190TBKT,F,3.3V Power Indicator LED
Y1,1,8MHz,Crystal_SMD_3225-4Pin_3.2x2.5mm,ABM8-8.000MHZ-B2-T,F,8 MHz HSE Crystal
Y2,1,32.768kHz,Crystal_SMD_3215-2Pin_3.2x1.5mm,ABS07-32.768KHZ-T,F,32.768 kHz LSE RTC Crystal
"C3, C4",2,18pF,C_0603_1608Metric,CC0603JRNPO9BN180,F,HSE Load Cap 1; HSE Load Cap 2
"C5, C6",2,12pF,C_0603_1608Metric,CC0603JRNPO9BN120,F,LSE Load Cap 1; LSE Load Cap 2
"R5, R6, R7, R8, R9, R10, R20, R11, R23, R25, R26, R36, R12, R13, R14, R15",16,10k,R_0603_1608Metric,RC0603FR-0710KL,B/F,SD_CS Pull-up; SPI1_MISO Pull-up; SPI1_MOSI Pull-up ...
"C21, C27",2,10uF,C_0805_2012Metric,CL21A106KAYNNNE,B/F,SD VDD Bulk Cap; Buck Input Decoupling Cap
"C22, C17, C19, C20, C31, C32, C1, C14, C8, C9, C10, C11, C2, C15, C16, C24, C25",17,100nF,C_0603_1608Metric,CC0603KRX7R7BB104,B/F,SD VDD Decoupling Cap; MPU-6050 REGOUT Cap; BMP280 VDD Decoupling ...
Q4,1,2N7002,SOT-23,2N7002LT1G,F,Beacon N-MOSFET Driver
R18,1,22R,R_0805_2012Metric,ERJ-6GEYJ220V,F,Beacon LED Current Limit
"R19, R16, R17",3,100R,R_0603_1608Metric,RC0603FR-07100RL,B/F,Beacon Gate Series R; USART1 TX -> ESP RXD0 Series; ESP TXD0 -> USART1 RX Series
"R21, R22",2,1k,R_0603_1608Metric,RC0603FR-071KL,F,Status LED Resistor; Power LED Resistor
"R3, R4",2,4.7k,R_0603_1608Metric,RC0603FR-074K7L,F,I2C1 SCL Pull-up; I2C1 SDA Pull-up
C18,1,2.2nF,C_0603_1608Metric,CC0603KRX7R9BB222,F,MPU-6050 CPOUT Charge Pump Cap
U5,1,CY15B102QN-50SXIT,SOIC-8_3.9x4.9mm_P1.27mm,CY15B102QN-50SXIT,B,2 Mbit SPI FRAM Non-Volatile Memory
"Q1, Q2, Q3",3,AO3401A,SOT-23,AO3401A,B,Reverse-Polarity P-MOSFET; Primary Battery Ideal Diode P-MOSFET; Supercap Backup Ideal Diode P-MOSFET
"C26, C13",2,1uF,C_0603_1608Metric,CL10A105KB8NNNC,B,Fast-Trip Input Cap; VDDA Bulk Cap
"U7, U8",2,LTC4412ES6,TSOT-23-6,LTC4412ES6#TRPBF,B,Primary Battery PowerPath Ideal Diode Ctrl; Supercap Backup Ideal Diode OR-ing Ctrl
U11,1,AP22814AW5,SOT-23-5,AP22814AW5-7,B,Slew-Limited Supercap Charge Switch
R24,1,15R,R_0805_2012Metric,ERJ-6GEYJ150V,B,Supercap Charge Current Limit (~200mA)
D4,1,B5819W,D_SOD-123,B5819W-7-F,B,Supercap Blocking Schottky Diode
U6,1,TPS62822DLC,Texas_VSON-HR-8_1.5x2mm_P0.5mm,TPS62822DLCR,B,3.3V 2A Synchronous Buck Regulator
L1,1,1.0uH_3.5A,L_Wuerth_MAPI-3015,74438334010,B,1.0uH Shielded Buck Power Inductor
"C28, C29, C23",3,22uF,C_0805_2012Metric,CL21A226MAYNNNE,B,Buck Output Bulk Cap 1; Buck Output Bulk Cap 2; ESP32 VDD Bulk Cap
R27,1,45.3k_1%,R_0603_1608Metric,RC0603FR-0745K3L,B,Buck FB Top (3.318V)
"R28, R31, R32, R34",4,10.0k_1%,R_0603_1608Metric,RC0603FR-0710KL,B,Buck FB Bottom; PFD Ref Divider Top (1.250V); PFD Ref Divider Bottom ...
C30,1,22pF,C_0603_1608Metric,CC0603JRNPO9BN220,B,Buck FB Feedforward Cap
R29,1,100k,R_0603_1608Metric,RC0603FR-07100KL,B,Buck PG Pull-up
U9,1,TLV7031DBV,SOT-23-5,TLV7031DBVR,B,PFD Comparator (3.00V Trip -> PB1 EXTI1)
U10,1,LM4040DBZ-2.5,SOT-23,LM4040AIM3-2.5,B,2.500V Precision Shunt Reference
R30,1,1.5k,R_0603_1608Metric,RC0603FR-071K5L,B,LM4040 Bias Resistor
R33,1,14.0k_1%,R_0603_1608Metric,RC0603FR-0714KL,B,PFD Sense Divider Top (3.00V)
R35,1,470k,R_0603_1608Metric,RC0603FR-07470KL,B,PFD Positive Hysteresis (~53mV)
R1,1,10k_0.1%,R_0603_1608Metric,ERA-3AEB103V,B,ADC1 Divider Top (0.1%)
R2,1,2k_0.1%,R_0603_1608Metric,ERA-3AEB202V,B,ADC1 Divider Bottom (0.1%)
FB1,1,600R@100MHz,L_0603_1608Metric,BLM18AG601SN1D,B,VDDA Analog Filter Bead
C7,1,2.2uF,C_0603_1608Metric,CL10A225KQ8NNNC,B,STM32 VCAP_1 Core Cap
C12,1,4.7uF,C_0603_1608Metric,CL10A475KQ8NNNC,B,MCU VDD Bulk Cap
